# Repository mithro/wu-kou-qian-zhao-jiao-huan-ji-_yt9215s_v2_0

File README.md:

# YT9215S 5-port gigabit Ethernet switch (基于裕太微YT9215S的五口千兆交换机)

A mirror of the open hardware project
**[基于裕太微YT9215S的五口千兆交换机](https://oshwhub.com/pankanwen/wu-kou-qian-zhao-jiao-huan-ji-_yt9215s_v2_0)**
("5-port gigabit Ethernet switch based on the Motorcomm YT9215S"), designed by
**[pankanwen](https://oshwhub.com/pankanwen)** and published on OSHWHub (立创开源硬件平台).

## Author and credit

All design work, photos and the original description in this repository are by
**pankanwen** ([oshwhub.com/pankanwen](https://oshwhub.com/pankanwen)). This repository
is only a mirror; the original project page is the canonical source:

* Project page: <https://oshwhub.com/pankanwen/wu-kou-qian-zhao-jiao-huan-ji-_yt9215s_v2_0>
* Open in EasyEDA Pro (嘉立创EDA专业版): <https://pro.lceda.cn/editor#id=81622a3a90204e8685b9f33b56559349>
* Created 2023-09-04, last updated 2023-10-26 (first published 2023-09-08)

Please credit pankanwen and link to the original project page in anything derived from it.

## License

The original project is published under
**[Creative Commons Attribution-NonCommercial-ShareAlike 3.0](https://creativecommons.org/licenses/by-nc-sa/3.0/)**
(CC BY-NC-SA 3.0), as declared on the OSHWHub project page. The full legal text is in
[LICENSE](LICENSE). In short: you may share and adapt it with attribution, **not for
commercial purposes**, and derivatives must use the same license.

The author also states (translated): *"The schematic and software of this project are for
learning and exchange only and must not be used for any commercial purpose."*

The mirror maintainer's additions (README, English translation, file reorganisation,
CSV conversions) are offered under the same license.

## What is it?

An unmanaged ("dumb") 5-port gigabit Ethernet switch built around the
[Motorcomm (裕太微电子)](https://www.motor-comm.com/) **YT9215S** switch chip.

* 5 × 10/100/1000BASE-T RJ45 ports (HanRun HR911130A jacks with integrated magnetics)
* Powered from USB Type-C (5 V), with a footprint for a 12 V DC barrel jack
* MT2492 buck converter for the core supply; option to use the YT9215S's internal 1.1 V DC-DC
* 25 MHz crystal, strap resistors for configuration, no EEPROM/flash required ("无需配置固件")
* 2-layer PCB, 100 mm × 65 mm (3937 × 2559 mil)
* Measured about 1.6 W with three ports active; a heatsink on the chip is recommended
  (over 75 °C without one)

The YT9215S is described as pin-to-pin compatible with the Realtek RTL8367S, and the
schematic symbol and BOM entry for U2 use the **RTL8367S-CG** part. The author reports that
an RTL8367S did *not* boot on this board, while the YT9215S works. **Fit a YT9215S for U2.**

See the full description: [English translation](docs/description.en.md) ·
[原文 (Chinese original)](docs/description.zh-CN.md).

## Repository contents

| Path | Contents |
| --- | --- |
| [`easyeda/`](easyeda/) | Full EasyEDA Pro project source: [`.epro2`](easyeda/YT9215S-5-port-switch.epro2) (current format) and [`.epro`](easyeda/YT9215S-5-port-switch.epro) (older Pro format). Open with EasyEDA Pro / 嘉立创EDA专业版 (File → Import / Open project); A KiCad conversion is in [`kicad/`](kicad/). |
| [`kicad/`](kicad/) | KiCad 9 project (schematic, PCB, libraries) converted from the [`.epro`](easyeda/YT9215S-5-port-switch.epro) with KiCad's own importer, plus renders and ERC/DRC reports. See [`kicad/README.md`](kicad/README.md) for what was fixed after import and what still differs. |
| [`schematic/`](schematic/) | Schematic as PDF (both sheets), per-sheet SVG and PNG, and EasyEDA netlist (`.enet`). Sheet 1: switch chip, power, crystal, LED, reset, fan header, fuse, inputs. Sheet 2: the five RJ45 ports. |
| [`pcb/`](pcb/) | PCB as PDF, 3D model (STEP), DXF, IPC-D-356A netlist, pick-and-place (XLSX and CSV), interactive BOM (HTML), board statistics and an editor screenshot. |
| [`gerber/`](gerber/) | Gerber and drill fabrication files (zip as exported by EasyEDA Pro, plus the extracted layers). See [`gerber/README.md`](gerber/README.md) for the file list, provenance and checks. |
| [`bom/`](bom/) | Bill of materials exported from EasyEDA (XLSX and CSV), with LCSC part numbers. |
| [`altium/`](altium/) | Altium Designer export (`.PrjPcb`, `.SchDoc` × 2, `.PcbDoc`) generated by EasyEDA Pro. |
| [`images/`](images/) | Photos and screenshots from the project page (built board, layout, strap pin table, test results). |
| [`attachments/`](attachments/) | Files attached to the project page: `YT9215S_Datasheet_draft_V0.1.pdf` and `裕太微电子产品选型20230308.pdf` (Motorcomm product selection guide, 2023-03-08). |
| [`docs/`](docs/) | Project description, original Chinese and English translation. |
| [`source/oshwhub/`](source/oshwhub/) | Raw project metadata and description HTML as returned by OSHWHub / EasyEDA, for provenance. |

### Not included

* **ODB++ files.** Not exported for this mirror; they can be generated from
  [`easyeda/*.epro2`](easyeda/YT9215S-5-port-switch.epro2) in EasyEDA Pro via *Export → ODB++*.
* The OSHWHub page lists no separate BOM or 3D-model attachments; the BOM and STEP here
  were exported from the design itself.
* User comments on the OSHWHub page (written by other people, not the author).

## How this mirror was made

Mirrored on 2026-10-22. The description, photos and attachments were downloaded from the
OSHWHub project page (attachment MD5s match the values OSHWHub reports). The design files
were exported, unmodified, from the public project using EasyEDA Pro's own export
functions (editor V4.1.78). The Gerber/drill files were exported on 2026-11-03 with
JLCEDA Pro V4.1.93 (*Export → PCB Fabrication File (Gerber)*, One Key Export, default
settings, design unmodified). Image files were renamed to descriptive names; the
mapping to OSHWHub's file names is in
[`source/oshwhub/image-filenames.md`](source/oshwhub/image-filenames.md).

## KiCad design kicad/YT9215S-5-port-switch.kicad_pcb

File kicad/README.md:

# KiCad version of the YT9215S 5-port switch

A KiCad 9 conversion of pankanwen's design, made with **KiCad's own EasyEDA Pro
importer** from [`../easyeda/YT9215S-5-port-switch.epro`](../easyeda/YT9215S-5-port-switch.epro), not redrawn by
hand. Same author, credit and licence (CC BY-NC-SA 3.0) as the rest of this repository;
see the [top-level README](../README.md).

Open [`YT9215S-5-port-switch.kicad_pro`](YT9215S-5-port-switch.kicad_pro) in KiCad 9.0 or newer.

## Files

| Path | Contents |
| --- | --- |
| [`YT9215S-5-port-switch.kicad_pro`](YT9215S-5-port-switch.kicad_pro) | Project (open this) |
| [`YT9215S-5-port-switch.kicad_sch`](YT9215S-5-port-switch.kicad_sch), [`1_P1.kicad_sch`](1_P1.kicad_sch), [`2_P2.kicad_sch`](2_P2.kicad_sch) | Schematic: root sheet, P1 (switch chip, power, crystal, LED, reset), P2 (five RJ45 ports) |
| [`YT9215S-5-port-switch.kicad_pcb`](YT9215S-5-port-switch.kicad_pcb) | PCB, 2 layers, 100 × 65 mm, zones filled |
| [`YT9215S-5--easyedapro.kicad_sym`](YT9215S-5--easyedapro.kicad_sym), [`YT9215S-5-port-switch.pretty/`](YT9215S-5-port-switch.pretty/) | Project symbol and footprint libraries written by the importer |
| [`render/`](render/) | Schematic [`schematic.pdf`](render/schematic.pdf), [`P1`](render/schematic-P1.png) and [`P2`](render/schematic-P2.png) PNGs; PCB [`pcb-layers.pdf`](render/pcb-layers.pdf) (one page per layer), [`top`](render/pcb-top-copper.png) and [`bottom`](render/pcb-bottom-copper.png) copper, [`top`](render/pcb-3d-top.png) and [`bottom`](render/pcb-3d-bottom.png) 3D |
| [`reports/`](reports/) | [`erc.rpt`](reports/erc.rpt), [`drc.rpt`](reports/drc.rpt) (with schematic parity), [`drc-exclusions.rpt`](reports/drc-exclusions.rpt), [`net-compare.txt`](reports/net-compare.txt) |
| [`tools/`](tools/) | Fix scripts [`fixup_import.py`](tools/fixup_import.py), [`fix_schematic_erc.py`](tools/fix_schematic_erc.py), [`fix_pcb_drc.py`](tools/fix_pcb_drc.py) (with helper [`sch_geometry.py`](tools/sch_geometry.py)), and [`compare_nets.py`](tools/compare_nets.py) (connectivity check) |

## How it was made

1. KiCad 9.0.9 (Ubuntu PPA), *Import Non-KiCad Project → EasyEDA (JLCEDA) Pro Project*
   on the [`.epro`](../easyeda/YT9215S-5-port-switch.epro) for the PCB, and *Schematic Editor → File → Import → Non-KiCad
   Schematic* on the same `.epro` for the schematic. The [`.epro2`](../easyeda/YT9215S-5-port-switch.epro2) file is a newer
   format that KiCad 9 can't read. The untouched importer output is the first commit
   that added this directory.
2. [`tools/fixup_import.py`](tools/fixup_import.py) (run with KiCad's Python) fixes the importer problems below.
   It is the second commit, so the diff shows exactly what changed.
3. [`tools/fix_schematic_erc.py`](tools/fix_schematic_erc.py) then [`tools/fix_pcb_drc.py`](tools/fix_pcb_drc.py) clear the remaining ERC,
   DRC and schematic-parity reports (third commit). Both scripts list each change with
   its reason at the top of each step.

### Rule checks

| Check | Raw import | After step 2 | Now |
| --- | --- | --- | --- |
| ERC | 613 | 353 | 0 |
| DRC | 1448 | 140 | 0 (4 excluded) |
| Unconnected | – | 1 | 0 |
| Schematic parity | – | 165 | 0 |
| Nets same in schematic and PCB | – | 77 of 157 | 117 of 117 |

The last row comes from [`compare_nets.py`](tools/compare_nets.py) ([`report`](reports/net-compare.txt)) and counts every net, including single-pin ones. An earlier version of this
README said the schematic and PCB matched; the check then skipped single-pin nets and
missed that the 40 Ethernet MDI nets were split in the schematic (see below).

The four DRC exclusions (in the [`project file`](YT9215S-5-port-switch.kicad_pro), each with a comment, listed in
[`reports/drc-exclusions.rpt`](reports/drc-exclusions.rpt)) are the shield holes that neighbouring RJ45 jacks share.
The five jacks are ganged at a 16 mm pitch and each jack's shield pin sits on its
edge, so RJ1's right shield and RJ2's left shield are one hole. EasyEDA's own drill file
drills these four holes twice as well. Changing that would mean redesigning the jack
footprint, so it is recorded as reviewed rather than changed.

### Importer problems found and fixed (step 2)

| Problem in the raw import | Effect | Fix |
| --- | --- | --- |
| SMD pads imported as through-hole[^smd] | Unmanufacturable; 61 shorts | Pads made SMD again |
| Wire net names became *local* labels | 10 LED nets cut between sheets | Global labels |
| Symbols point at a missing footprint library | 249 ERC warnings | Footprints set from the PCB |
| Case-only duplicate footprints | Breaks macOS/Windows checkouts | Duplicates removed |
| PCB footprint values empty | No values on the board | Copied from the schematic |
| EasyEDA design rules not imported | ~500 false clearance errors | 4 mil clearance, 10 mil track, 24/12 mil via |
| Copper zones not filled | | Zones refilled |

[^smd]: The [`.epro`](../easyeda/YT9215S-5-port-switch.epro) stores every SMD pad with a 0.001 mm placeholder hole, and the
importer turned all 367 SMD pads into all-layer through-hole pads. Pads with a hole
under 0.01 mm become SMD pads on their footprint's side: 250 top, 117 bottom and 89 PTH
pads, which is what EasyEDA's board statistics report ([`../pcb/pcb-info.txt`](../pcb/pcb-info.txt)).

### Schematic fixes (step 3, [`fix_schematic_erc.py`](tools/fix_schematic_erc.py))

* **Ethernet nets joined.** EasyEDA net labels are global across sheets. The importer
  made them local, so the 40 MDI nets between the switch chip (sheet P1) and the RJ45
  jacks (sheet P2) were cut in two. Labels used on more than one sheet are now global.
  This was a real connectivity error in the step 2 version, not just a warning.
* **Pin types.** EasyEDA gives every pin the default type "IN". These carry no design
  intent and became passive.
* **Power symbols.** The importer gave every power port one shared symbol whose pin was
  named after the first net it saw. Each power net now has its own power symbol, and a
  PWR_FLAG marks each power net that has no driving pin (13 nets).
* **Label wiring.** EasyEDA lets a net label sit part-way along a wire or just past its
  end. 21 labels moved to the wire end, and 2 dangling stubs were removed.
* **Unused pins.** No-connect flags on the 6 U2 pins that are unconnected on the PCB
  too (I²C, unused GPIO).
* Test points get the value "TestPoint". The two drawing-frame symbols are excluded
  from the board and BOM. MT2492 and the frame symbol, which existed in two versions
  under one name, get one library symbol per version.

### PCB fixes (step 3, [`fix_pcb_drc.py`](tools/fix_pcb_drc.py))

Fixed in the board:

* **USB-C shell.** The four shell tabs are GND in EasyEDA, but the importer kept the net
  on only two, so GND tracks into the other two were reported as shorts.
* **Keepouts.** EasyEDA "no copper pour" regions became full keepouts, which flagged the
  routed buck-converter and crystal tracks. They now keep out pour only.
* **Holes.** The four 3.2 mm mounting holes were imported as drawings on Edge.Cuts,
  so the board had none. They are NPTH holes again (MH1–MH4), and so are the RJ45
  plastic pegs. Two doubled vias were removed.
* **Crystal ground (design flaw).** X1's GND pads 2 and 4 are joined to each other but
  to nothing else. No pour reaches them in the EasyEDA design either, so the crystal's
  ground pads float. A GND via next to pad 2 now ties them to the bottom ground pour.
* **Names and values.** Nets renamed and values updated as *Update PCB from
  Schematic* would (33 nets, 16 values). Unused U2 pins get KiCad's
  `unconnected-(…)` nets. U2's exposed pad, a free pad in EasyEDA, is footprint EP1.
* **Placement.** RJ3 sat 0.034 mm off the jack pitch, so its shield holes were
  0.034 mm off the neighbours'. It is moved onto the pitch. Test pad TP10 moved 0.3 mm
  off C43's outline. The JLC order-number text moved off U2's exposed pad to the top
  left.
* **Rules.** Board-edge clearance is EasyEDA's 11.8 mil (0.3 mm), not KiCad's 0.5 mm
  default. One GND track sits 0.36 mm from the edge.
* The title text uses KiCad's font (Century Gothic isn't available). Three pads with a
  single thermal spoke into the GND pour are connected solidly.

Fixed in the footprint library:

* **RJ45 jack.** The library copy now has the NPTH pegs. Its outline sat on the edge
  line it shares with the next jack and ran over the shield pads. It is moved in by
  0.15 mm and broken around the pads. The courtyard follows the jack body, so ganged
  jacks no longer overlap.
* **USB-C and DC jack.** Outline clipped at the board edge (the USB-C receptacle
  overhangs it) and around RJ5's shield pad.
* **Test points** have no courtyard. They are bare pads with no part body.
* **6.3 mm electrolytic** (C2, C6) courtyard uses IPC-7351's 0.1 mm margin. The pads
  are 0.21 mm apart, as designed.
* **Library sync.** EasyEDA keeps a separate copy of each placed footprint, and rotation
  left sub-micron differences from the library copy (52 footprints). They are given the
  library graphics, as *Update Footprints from Library* would do. Pad positions are
  checked to match first.

### Not converted

* **3D models.** The [`.epro`](../easyeda/YT9215S-5-port-switch.epro) has no component 3D models, so KiCad's 3D view shows bare
  pads. The board's STEP model is in [`../pcb/pcb-3d.step`](../pcb/pcb-3d.step).
* The U2 symbol is still the RTL8367S-CG symbol from the original design; fit a YT9215S
  (see the [top-level README](../README.md)).

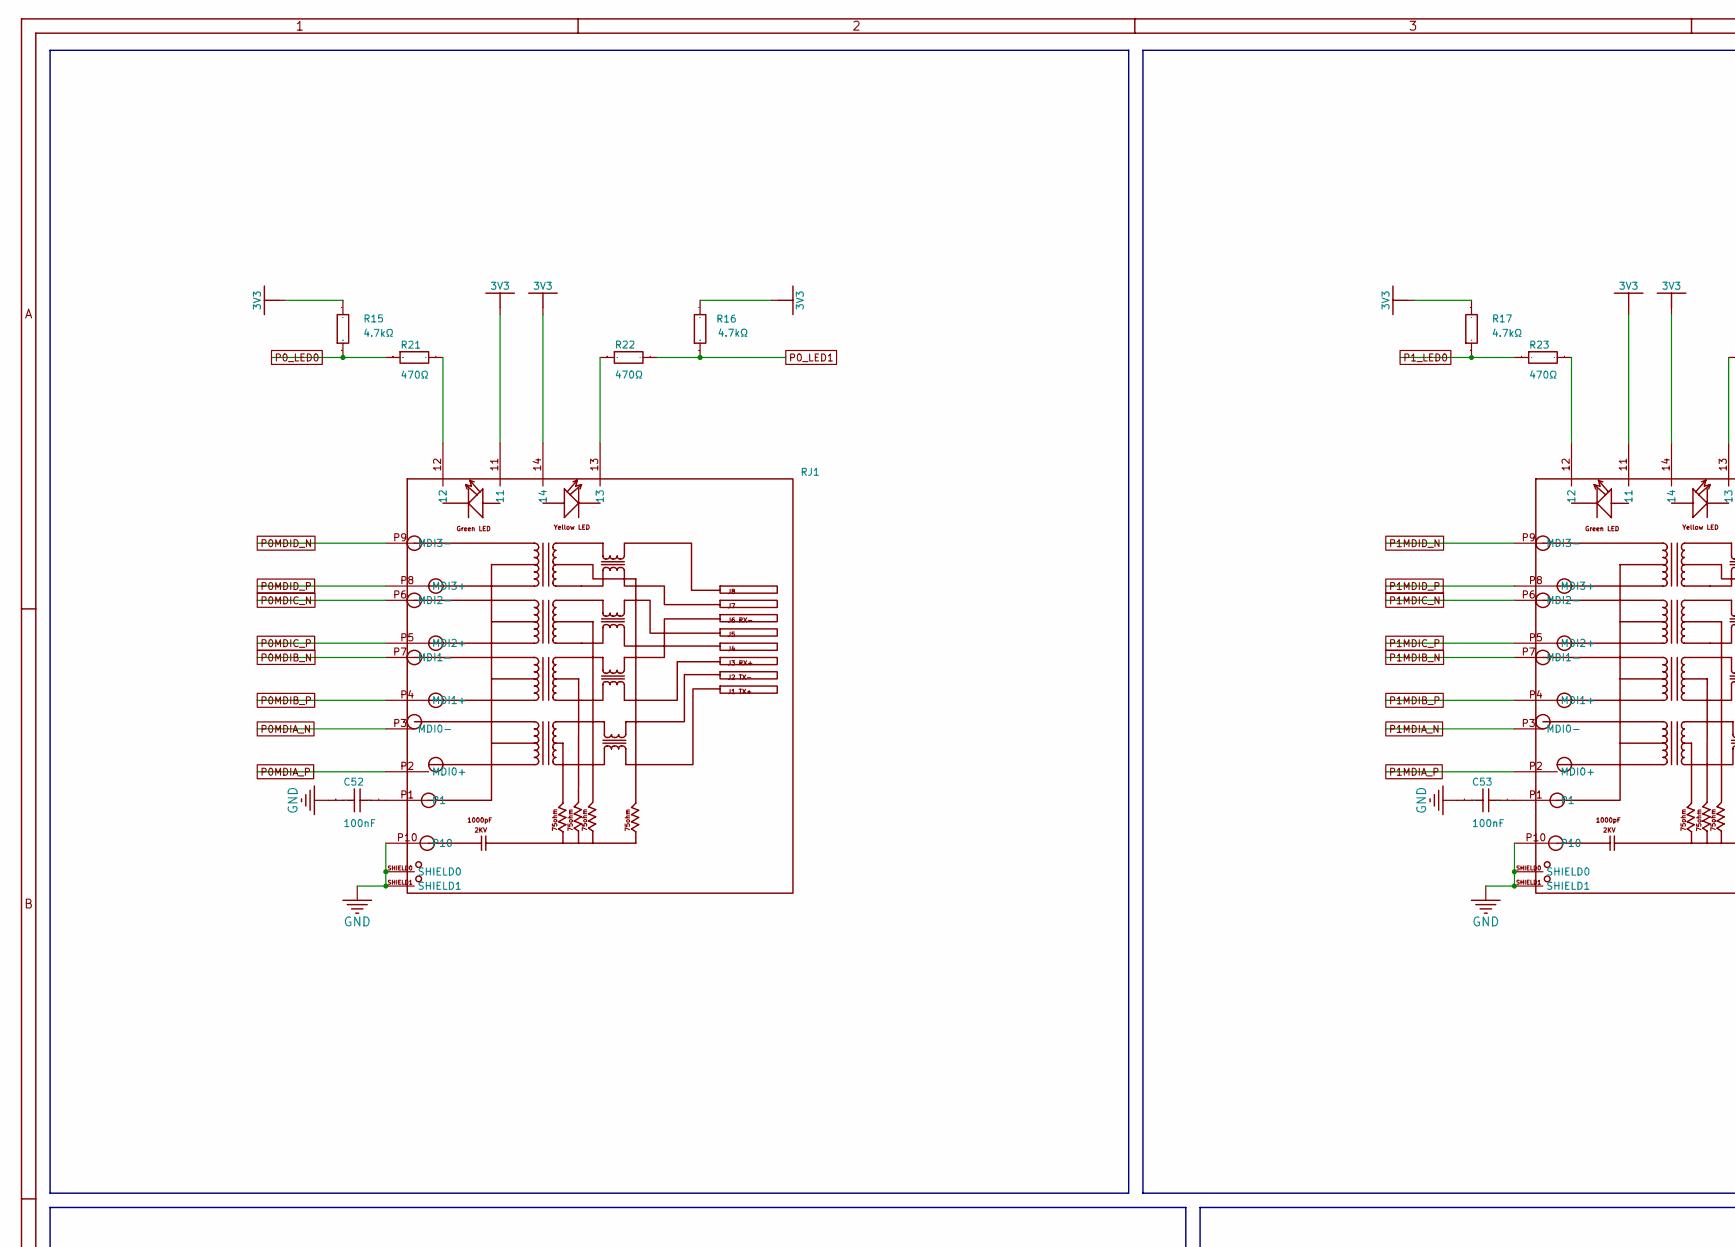
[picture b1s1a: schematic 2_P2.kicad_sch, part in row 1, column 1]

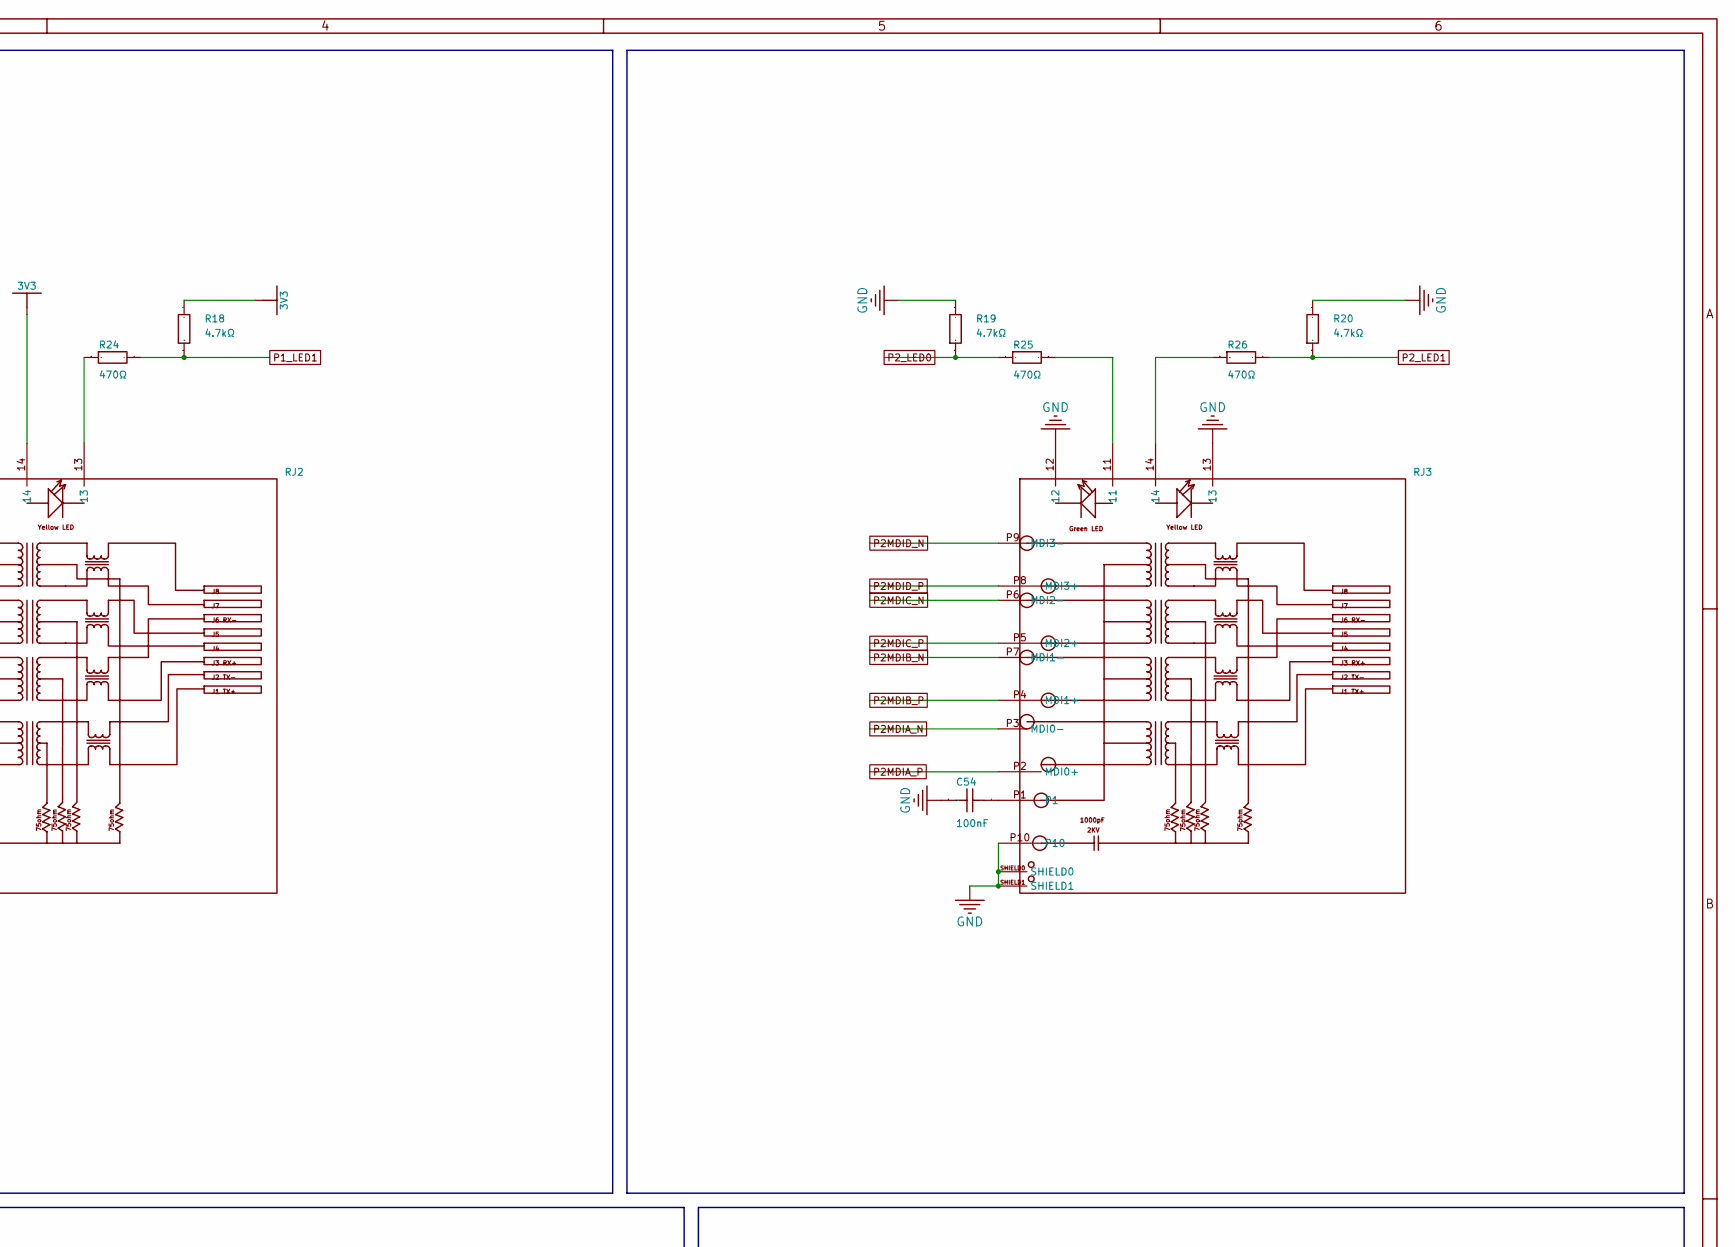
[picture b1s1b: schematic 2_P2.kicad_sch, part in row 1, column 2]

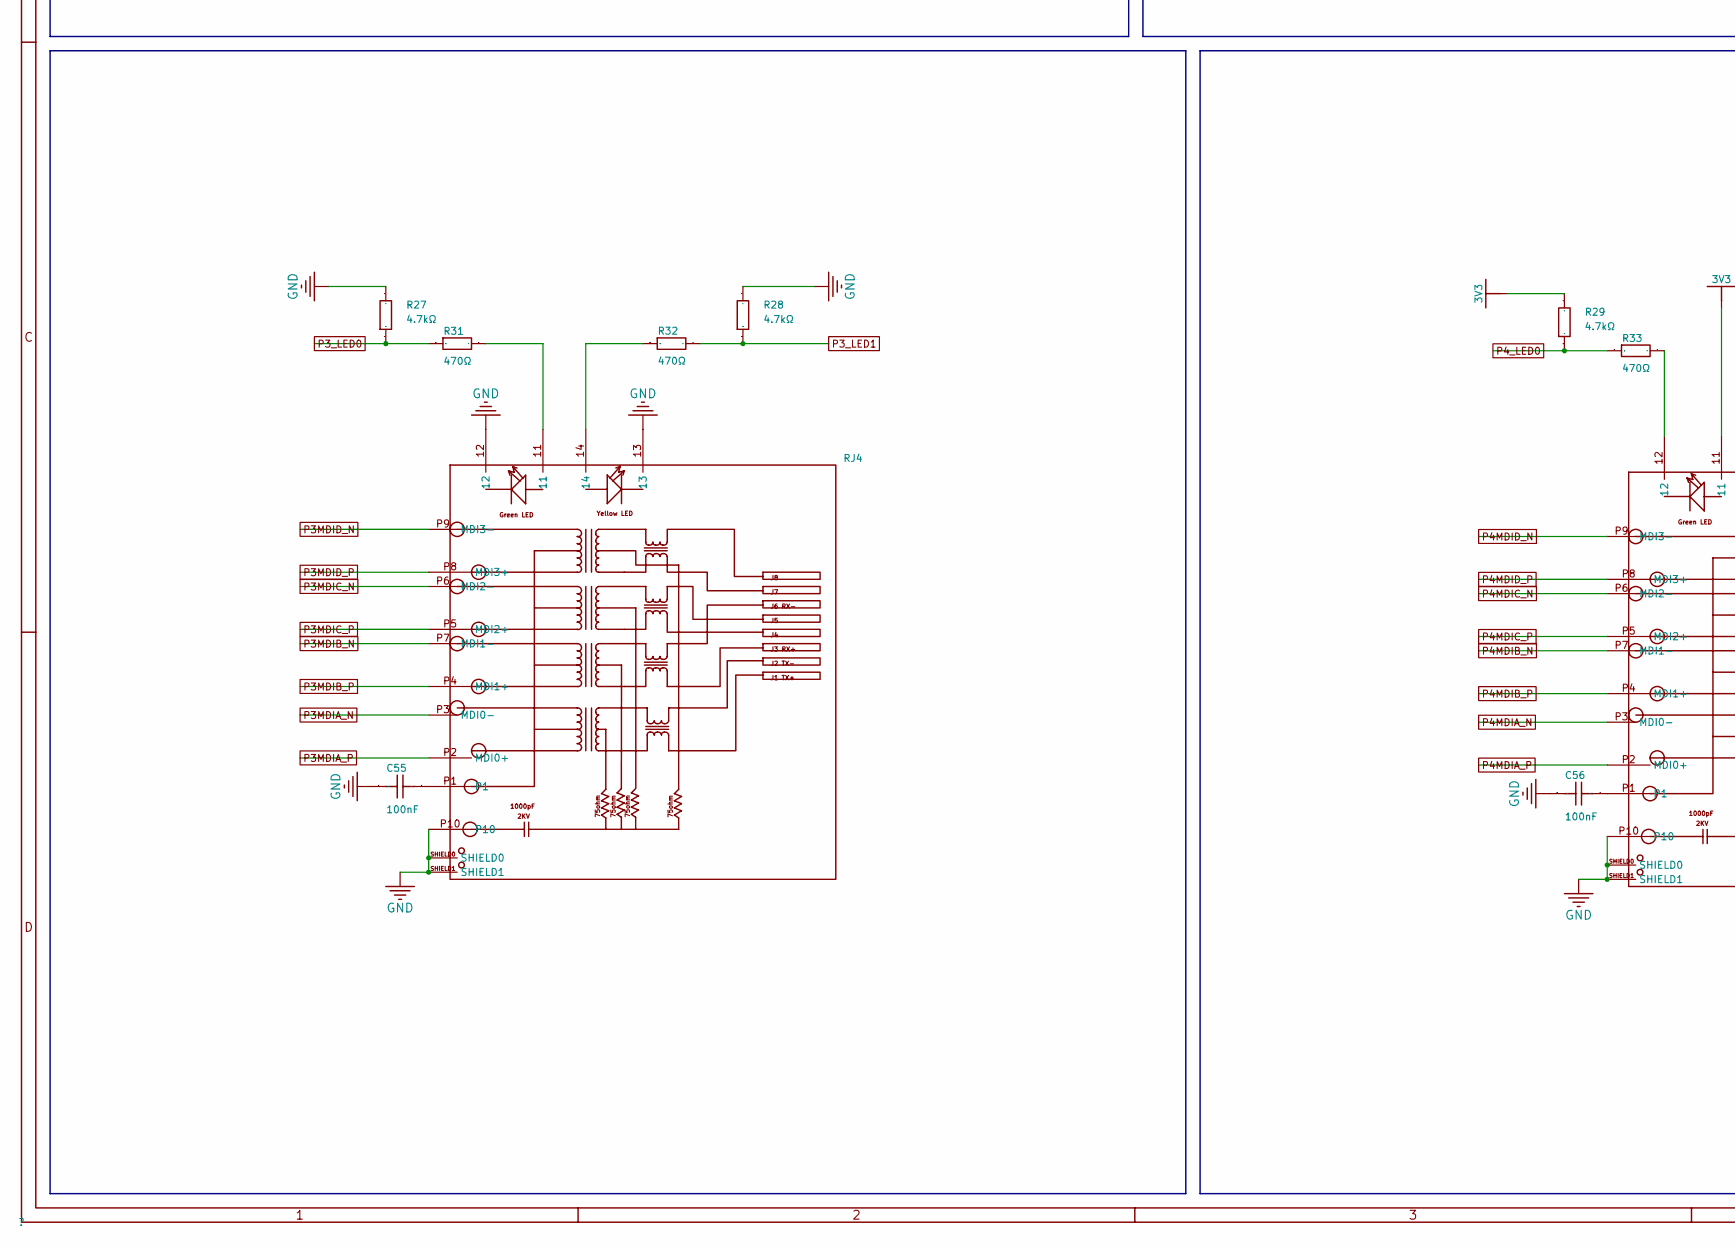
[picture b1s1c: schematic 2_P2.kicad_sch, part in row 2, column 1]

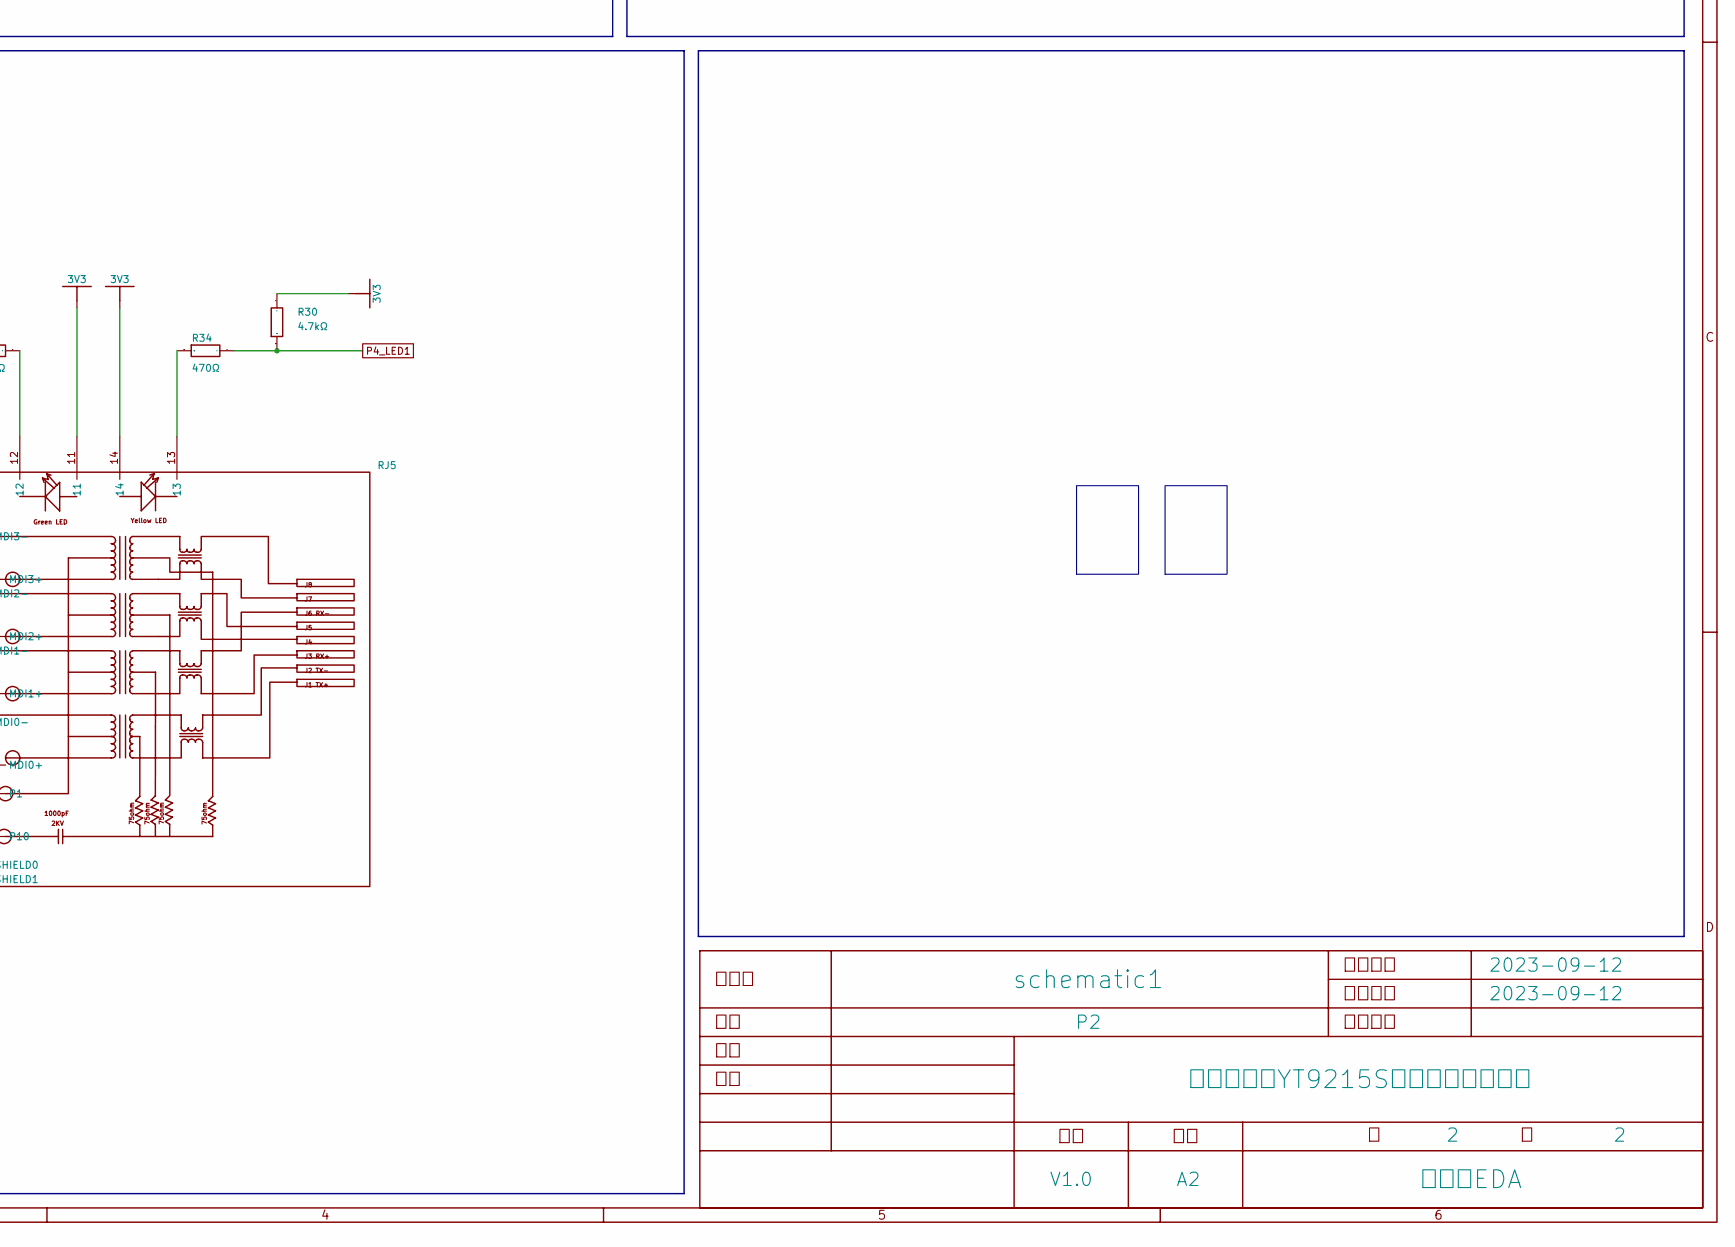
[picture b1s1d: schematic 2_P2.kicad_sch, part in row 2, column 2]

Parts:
C52, C53, C54, C55, C56: 100nF; C0402; Manufacturer Part FN15X104K250PNG; LCSC Part Name 100nF ±10% 25V
R15, R16, R17, R18, R19, R20, R27, R28, R29, R30: 4.7kΩ; R0402; Manufacturer Part 0402WGF4701TCE; LCSC Part Name 4.7kΩ ±1% 62.5mW
R21, R22, R23, R24, R25, R26, R31, R32, R33, R34: 470Ω; R0402; Manufacturer Part 0402WGF4700TCE; LCSC Part Name 470Ω ±1% 62.5mW
RJ1, RJ2, RJ3, RJ4, RJ5: HR911130A; RJ45-TH_HR911130A; Manufacturer Part HR911130A; LCSC Part Name HR911130A

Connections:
3V3: R15.2, R16.2, R17.2, R18.2, R29.2, R30.2, RJ1.11, RJ1.14, RJ2.11, RJ2.14, RJ5.11, RJ5.14; also elsewhere on the board
GND: C52.1, C53.1, C54.1, C55.1, C56.1, R19.2, R20.2, R27.2, R28.2, RJ1.P10, RJ1.SHIELD0, RJ1.SHIELD1, RJ2.P10, RJ2.SHIELD0, RJ2.SHIELD1, RJ3.12, RJ3.13, RJ3.P10, RJ3.SHIELD0, RJ3.SHIELD1, RJ4.12, RJ4.13, RJ4.P10, RJ4.SHIELD0, RJ4.SHIELD1, RJ5.P10, RJ5.SHIELD0, RJ5.SHIELD1; also elsewhere on the board
unnamed: C52.2, RJ1.P1
unnamed: C53.2, RJ2.P1
unnamed: C54.2, RJ3.P1
unnamed: C55.2, RJ4.P1
unnamed: C56.2, RJ5.P1
unnamed: R21.2, RJ1.12
unnamed: R22.1, RJ1.13
unnamed: R23.2, RJ2.12
unnamed: R24.1, RJ2.13
unnamed: R25.2, RJ3.11
unnamed: R26.1, RJ3.14
unnamed: R31.2, RJ4.11
unnamed: R32.1, RJ4.14
unnamed: R33.2, RJ5.12
unnamed: R34.1, RJ5.13
P0MDIA_N: RJ1.P3 (MDI0-); also elsewhere on the board
P0MDIA_P: RJ1.P2 (MDI0+); also elsewhere on the board
P0MDIB_N: RJ1.P7 (MDI1-); also elsewhere on the board
P0MDIB_P: RJ1.P4 (MDI1+); also elsewhere on the board
P0MDIC_N: RJ1.P6 (MDI2-); also elsewhere on the board
P0MDIC_P: RJ1.P5 (MDI2+); also elsewhere on the board
P0MDID_N: RJ1.P9 (MDI3-); also elsewhere on the board
P0MDID_P: RJ1.P8 (MDI3+); also elsewhere on the board
P0_LED0: R15.1, R21.1; also elsewhere on the board
P0_LED1: R16.1, R22.2; also elsewhere on the board
P1MDIA_N: RJ2.P3 (MDI0-); also elsewhere on the board
P1MDIA_P: RJ2.P2 (MDI0+); also elsewhere on the board
P1MDIB_N: RJ2.P7 (MDI1-); also elsewhere on the board
P1MDIB_P: RJ2.P4 (MDI1+); also elsewhere on the board
P1MDIC_N: RJ2.P6 (MDI2-); also elsewhere on the board
P1MDIC_P: RJ2.P5 (MDI2+); also elsewhere on the board
P1MDID_N: RJ2.P9 (MDI3-); also elsewhere on the board
P1MDID_P: RJ2.P8 (MDI3+); also elsewhere on the board
P1_LED0: R17.1, R23.1; also elsewhere on the board
P1_LED1: R18.1, R24.2; also elsewhere on the board
P2MDIA_N: RJ3.P3 (MDI0-); also elsewhere on the board
P2MDIA_P: RJ3.P2 (MDI0+); also elsewhere on the board
P2MDIB_N: RJ3.P7 (MDI1-); also elsewhere on the board
P2MDIB_P: RJ3.P4 (MDI1+); also elsewhere on the board
P2MDIC_N: RJ3.P6 (MDI2-); also elsewhere on the board
P2MDIC_P: RJ3.P5 (MDI2+); also elsewhere on the board
P2MDID_N: RJ3.P9 (MDI3-); also elsewhere on the board
P2MDID_P: RJ3.P8 (MDI3+); also elsewhere on the board
P2_LED0: R19.1, R25.1; also elsewhere on the board
P2_LED1: R20.1, R26.2; also elsewhere on the board
P3MDIA_N: RJ4.P3 (MDI0-); also elsewhere on the board
P3MDIA_P: RJ4.P2 (MDI0+); also elsewhere on the board
P3MDIB_N: RJ4.P7 (MDI1-); also elsewhere on the board
P3MDIB_P: RJ4.P4 (MDI1+); also elsewhere on the board
P3MDIC_N: RJ4.P6 (MDI2-); also elsewhere on the board
P3MDIC_P: RJ4.P5 (MDI2+); also elsewhere on the board
P3MDID_N: RJ4.P9 (MDI3-); also elsewhere on the board
P3MDID_P: RJ4.P8 (MDI3+); also elsewhere on the board
P3_LED0: R27.1, R31.1; also elsewhere on the board
P3_LED1: R28.1, R32.2; also elsewhere on the board
P4MDIA_N: RJ5.P3 (MDI0-); also elsewhere on the board
P4MDIA_P: RJ5.P2 (MDI0+); also elsewhere on the board
P4MDIB_N: RJ5.P7 (MDI1-); also elsewhere on the board
P4MDIB_P: RJ5.P4 (MDI1+); also elsewhere on the board
P4MDIC_N: RJ5.P6 (MDI2-); also elsewhere on the board
P4MDIC_P: RJ5.P5 (MDI2+); also elsewhere on the board
P4MDID_N: RJ5.P9 (MDI3-); also elsewhere on the board
P4MDID_P: RJ5.P8 (MDI3+); also elsewhere on the board
P4_LED0: R29.1, R33.1; also elsewhere on the board
P4_LED1: R30.1, R34.2; also elsewhere on the board
